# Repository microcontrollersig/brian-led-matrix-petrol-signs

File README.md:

# Big LED Matrix from Petrol Pump Signage

#### Info

Not the usual HUB08/HUB12/HUB40/HUB75 style setup. Inner workings [here](https://github.com/microcontrollersig/brian-led-matrix-petrol-signs/blob/main/REVERSEENGINEER.md)

They usually come in 6 panels wide, 2 panels height (effectively becomes a 96x32 single-color LED matrix)

# PCB Controller for LED matrix

#### Bill of Materials

| Qty |                                                                                                                                                                                             | Code                                                                                                          | Where to Buy                                                                                                                                                                                                                                                                                                                                                                                            | Required |
| --- | ------------------------------------------------------------------------------------------------------------------------------------------------------------------------------------------- | ------------------------------------------------------------------------------------------------------------- | ------------------------------------------------------------------------------------------------------------------------------------------------------------------------------------------------------------------------------------------------------------------------------------------------------------------------------------------------------------------------------------------------------- | -------- |
| 1   |                                                                                    | [Raspberry Pico](https://www.raspberrypi.org/documentation/rp2040/getting-started/)                           | [Pi Australia](https://raspberry.piaustralia.com.au/products/raspberry-pi-pico?variant=32587824070705)<br/>[Altronics](https://www.altronics.com.au/p/z6421-raspberry-pi-pico-microcontroller-board/)<br/>[Element 14](https://au.element14.com/raspberry-pi/raspberry-pi-pico/raspberry-pi-32bit-arm-cortex/dp/3643332)<br/>[Core Electronics](https://core-electronics.com.au/raspberry-pi-pico.html) | Y        |
| 1   |                                                                          | [ESP8266 Wemos D1 mini](https://www.wemos.cc/en/latest/d1/d1_mini.html)                                       | [Aliexpress - color: d1 mini](https://www.aliexpress.com/item/32651747570.html)                                                                                                                                                                                                                                                                                                                         | Y        |
| 1   |                                       | [16 Pin IDC Locking Vertical Header](https://www.jaycar.com.au/16-pin-idc-locking-vertical-header/p/PP1138)   | 16-pin ribbon header                                                                                                                                                                                                                                                                                                                                                                                    | Y        |
| 1   |                                                                  | [3.5A buck converter - color: 5V](https://www.aliexpress.com/item/33036075561.html)                           | Buck converter                                                                                                                                                                                                                                                                                                                                                                                          | Y        |
| 1   |                                                                                                                      | [Terminal block](https://www.altronics.com.au/p/p2041a-dinkle-3-way-5.08mm-pcb-mount-terminal-block/)         | External power source                                                                                                                                                                                                                                                                                                                                                                                   | Y        |
| 1   |                      | [Disk Drive Power Connector Socket](https://www.jaycar.com.au/disk-drive-power-connector-socket/p/PS0742)     | Power connector from LEDs to terminal block                                                                                                                                                                                                                                                                                                                                                             | N        |
| 1   |                                                 | [Female header](https://www.jaycar.com.au/40-pin-female-header-strip/p/HM3230)                                | Female header for Pico                                                                                                                                                                                                                                                                                                                                                                                  | Y        |
| 1   |                                             | [Right-angle connector ](https://www.rockby.com.au/CatresultsSql_12.cfm?select=33&subcode=142&stock_no=27464) | Need for connecting buck converter                                                                                                                                                                                                                                                                                                                                                                      | Y        |
| 1   |  | [Round Female Pin Header connector - snapable](https://www.aliexpress.com/item/32848204130.html)              | Aliexpress                                                                                                                                                                                                                                                                                                                                                                                              | N        |
| 1   |                                                           | [2N2222A NPN transistor](https://www.jaycar.com.au/2n2222a-npn-transistor/p/ZT2298)                           | Pico software-controlled reset switch                                                                                                                                                                                                                                                                                                                                                                   | N        |

#### EAGLE Schematic for PCB Board

#### EAGLE Board file for PCB Board

### PCB Top Layer

#### PCB Bottom Layer

#### Raspberry Pi Pico

#### ESP8266 wemos d1 mini

# Software

Steps needed to complete software setup:

- Firmware needs to be uploaded to Pico, firmware also need to be uploaded to esp8266 D1 mini.
- wifi configuration of D1 mini.

In order to complete these steps, must first do the following steps on your computer:

- Download zip file containing firmware files and CH340 Windows driver for D1 mini from [here](https://github.com/microcontrollersig/brian-led-matrix-petrol-signs/releases/latest/download/brian-petrol-signs-easy-firmware-upload.zip) . Unzip the file to a known location on your computer.
- Download a ESP8266 flash utility. There are a number available, my preferred one is ESPHome-Flasher, which can be
  downloaded from [here](https://github.com/esphome/esphome-flasher/releases) .

## Uploading firmware to Raspberry Pico

[Click here for details](https://github.com/microcontrollersig/brian-led-matrix-petrol-signs/tree/main/code/pico).

## Uploading firmware to D1 mini and configuring wifi

[Click here for details](https://github.com/microcontrollersig/brian-led-matrix-petrol-signs/tree/main/code/d1mini)

# Roles of Microprocessors

## Pico

- update LED matrix
- receive commands from the D1 mini via serial(RX).

## ESP8266 D1mini

- Present user with web interface for controlling LED matrix.
- Send commands for the Pico to execute on the LED matrix via Serial(TX).

# References

- [How LED matrix was reverse engineered](https://github.com/microcontrollersig/brian-led-matrix-petrol-signs/blob/main/REVERSEENGINEER.md)

- [Eagle files](https://github.com/microcontrollersig/brian-led-matrix-petrol-signs/tree/main/eagle)

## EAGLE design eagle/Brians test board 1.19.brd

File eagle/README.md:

# Eagle Files

Latest version is v1.18

# JLCPCB
[JLCPCB gerber viewer at checkout](https://cart.jlcpcb.com/quote?orderType=1&stencilWidth=100&stencilLength=100&stencilCounts=5&stencilLayer=2&stencilPly=1.6&steelmeshSellingPriceRecordNum=A8256537-5522-491C-965C-646F5842AEC9&purchaseNumber=)

[gerber viewer](https://www.pcbway.com/project/OnlineGerberViewer.html)

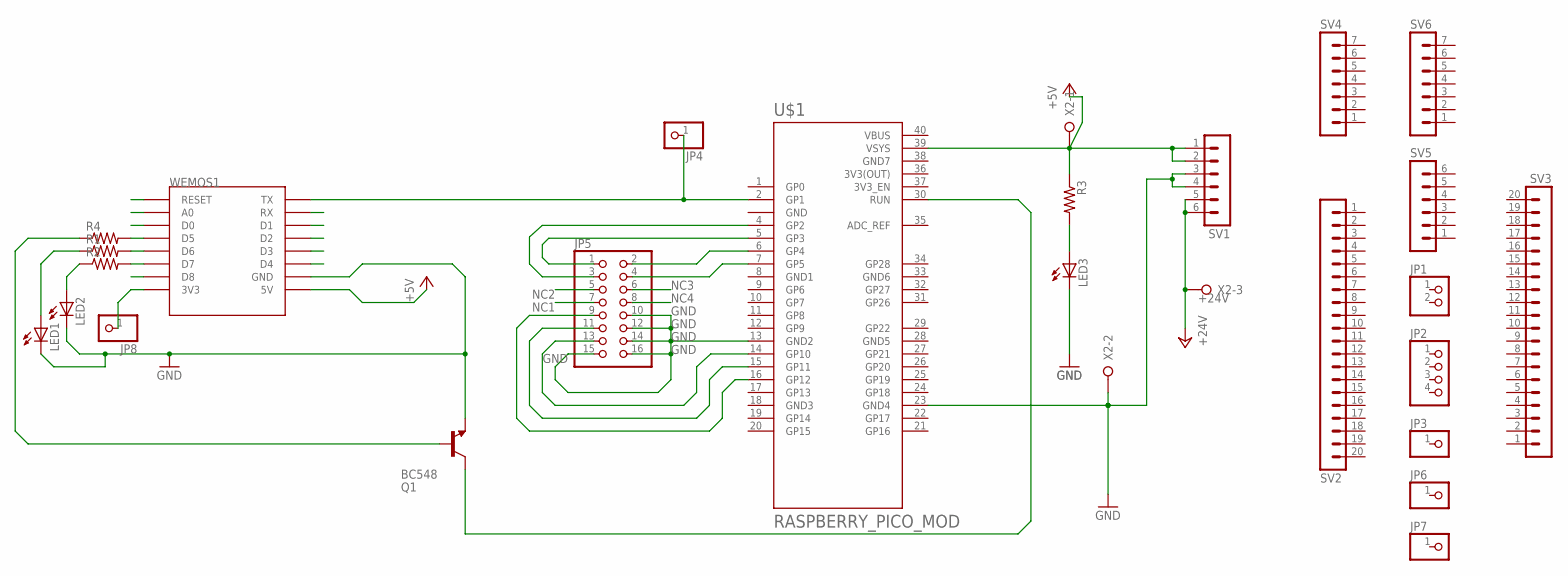
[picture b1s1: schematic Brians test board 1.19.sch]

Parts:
JP1: PINHD-1X2; 1X02
JP2: PINHD-1X4; 1X04
JP3, JP4, JP6, JP7, JP8: PINHD-1X1; 1X01
JP5: PINHD-2X8; 2X08
LED1, LED2, LED3: LED3MM
Q1: BC548; TO92-EBC
R1, R2, R4: R-US_0204/2V; 0204V
R3: R-US_0207/10; 0207/10
SV1, SV5: MA06-1
SV2, SV3: MA20-1
SV4, SV6: MA07-1
U$1: RASPBERRY_PICO_MOD; PICO-PKG-TH-LED
WEMOS1: WEMOS-D1-MINI
X2: W237-3E

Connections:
3V3(OUT): U$1.36 (3V3(OUT))
+5V: R3.1, SV1.1, SV1.2, U$1.39 (VSYS), WEMOS1.5V, X2.1
+24V: SV1.5, SV1.6, X2.3
A0: WEMOS1.A0
D0: WEMOS1.D0
D1: WEMOS1.D1
D2: WEMOS1.D2
D3: WEMOS1.D3
D4: WEMOS1.D4
D8: WEMOS1.D8
GND: JP5.10, JP5.12, JP5.14, JP5.15, JP5.16, LED1.K (C), LED2.K (C), LED3.K (C), Q1.E, SV1.3, SV1.4, U$1.3 (GND), U$1.13 (GND2), U$1.23 (GND4), WEMOS1.GND, X2.2
GND1: U$1.8 (GND1)
GND3: U$1.18 (GND3)
GND5: U$1.28 (GND5)
GND6: U$1.33 (GND6)
GND7: U$1.38 (GND7)
unnamed: JP5.1, U$1.5 (GP3)
unnamed: JP8.1, WEMOS1.3V3
unnamed: Q1.C, U$1.30 (RUN)
unnamed: JP4.1, U$1.2 (GP1), WEMOS1.TX
unnamed: JP5.3, U$1.4 (GP2)
unnamed: R2.2, WEMOS1.D7
unnamed: JP5.13, U$1.14 (GP10)
unnamed: JP5.11, U$1.15 (GP11)
unnamed: JP5.9, U$1.16 (GP12)
unnamed: JP5.2, U$1.6 (GP4)
unnamed: JP5.4, U$1.7 (GP5)
unnamed: R1.2, WEMOS1.D6
unnamed: LED2.A, R2.1
unnamed: LED1.A, R1.1
unnamed: LED3.A, R3.2
unnamed: R4.2, WEMOS1.D5
unnamed: Q1.B, R4.1
NC1: JP5.7
NC2: JP5.5
NC3: JP5.6
NC4: JP5.8
RST: WEMOS1.RESET
RX: WEMOS1.RX
VBUS: U$1.40 (VBUS)

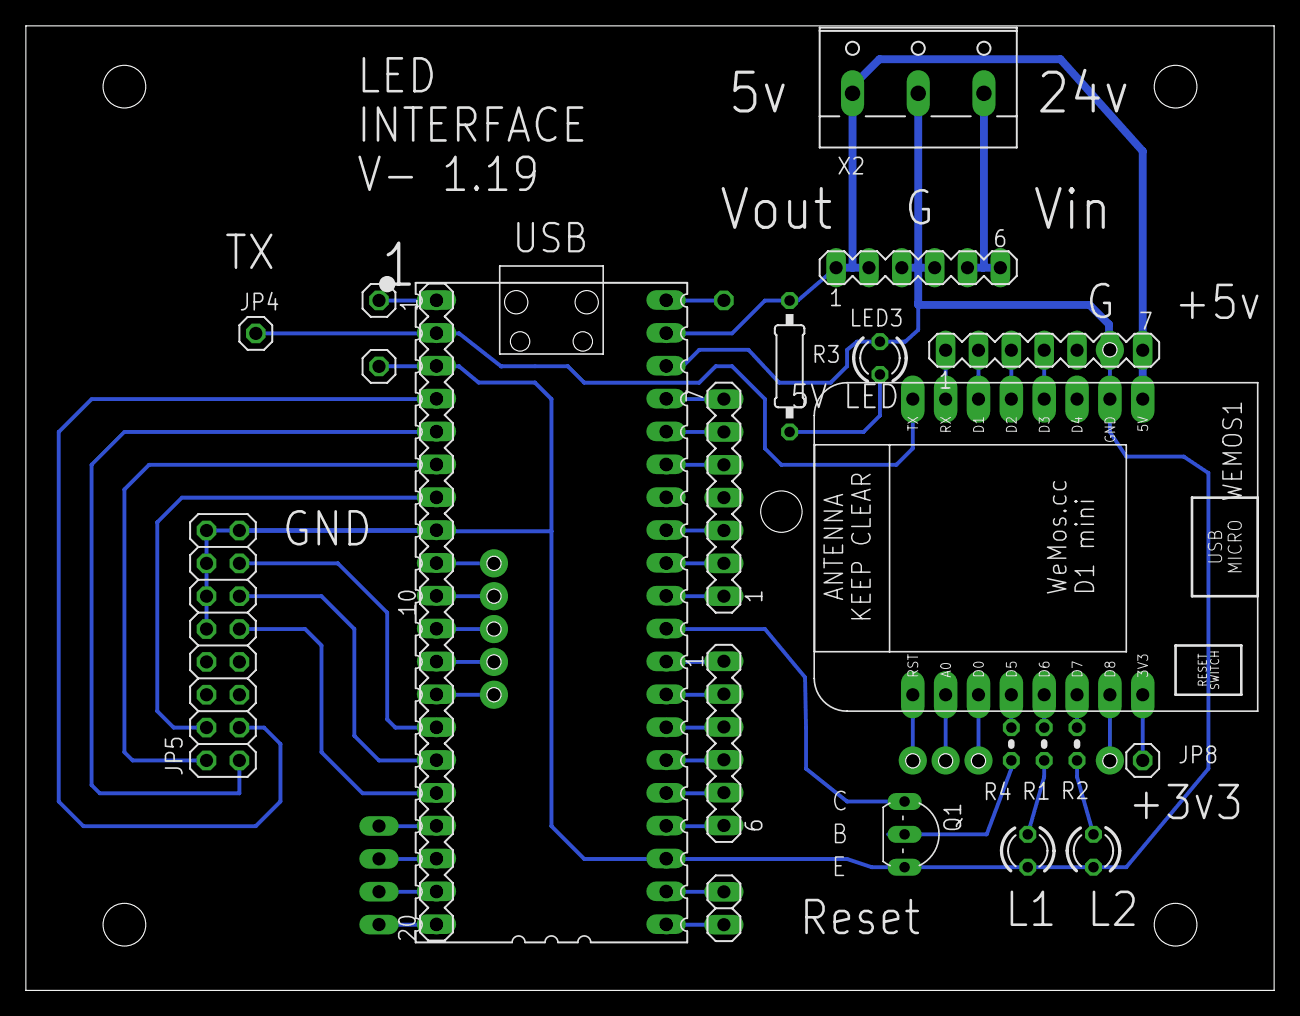
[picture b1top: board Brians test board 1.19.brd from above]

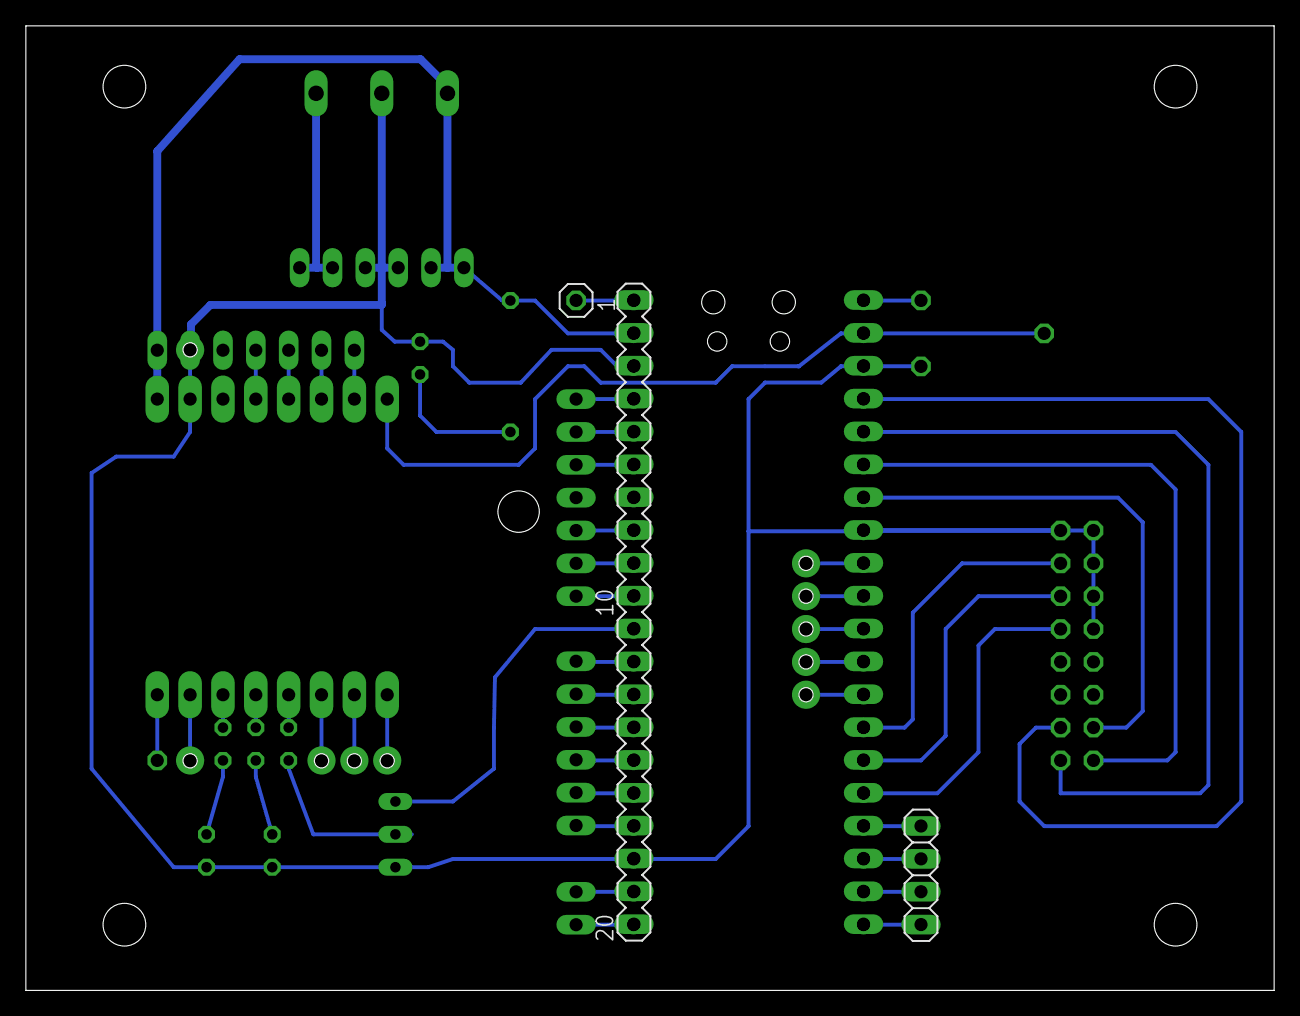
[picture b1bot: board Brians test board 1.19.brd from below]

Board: 2 copper layers, 96.5 x 74.6 mm, 25 parts (3 on the bottom side), 20 nets.

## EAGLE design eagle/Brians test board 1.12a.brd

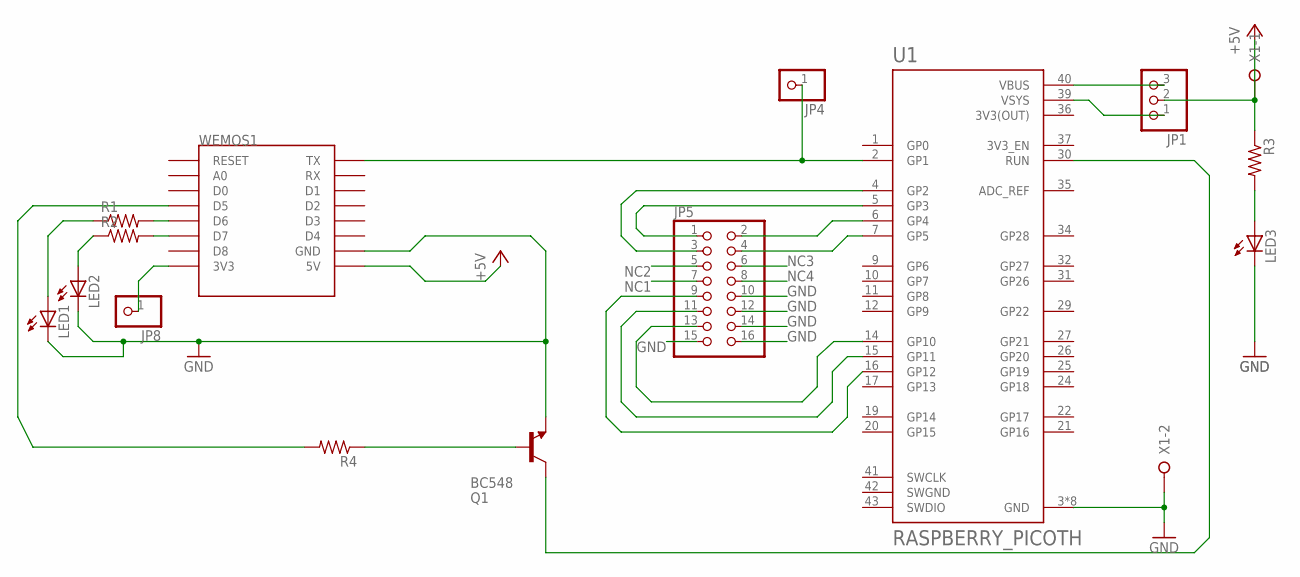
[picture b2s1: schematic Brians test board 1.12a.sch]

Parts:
JP1: PINHD-1X3; 1X03
JP4, JP8: PINHD-1X1; 1X01
JP5: PINHD-2X8; 2X08
LED1, LED2, LED3: LED3MM
Q1: BC548; TO92-EBC
R1, R2, R4: R-US_0204/2V; 0204V
R3: R-US_0207/10; 0207/10
U1: RASPBERRY_PICOTH; PICO-PKG-TH
WEMOS1: WEMOS-D1-MINI
X1: W237-02P; W237-132

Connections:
3V3(OUT): U1.36 (3V3(OUT))
+5V: JP1.2, R3.1, WEMOS1.5V, X1.1
GND: JP5.10, JP5.12, JP5.14, JP5.15, JP5.16, LED1.K (C), LED2.K (C), LED3.K (C), Q1.E, U1.3 (GND), U1.8 (GND), U1.13 (GND), U1.18 (GND), U1.23 (GND), U1.28 (GND), U1.33 (GND), U1.38 (GND), WEMOS1.GND, X1.2
unnamed: JP5.1, U1.5 (GP3)
unnamed: JP8.1, WEMOS1.3V3
unnamed: JP1.3, U1.40 (VBUS)
unnamed: Q1.C, U1.30 (RUN)
unnamed: JP4.1, U1.2 (GP1), WEMOS1.TX
unnamed: JP5.3, U1.4 (GP2)
unnamed: R2.2, WEMOS1.D7
unnamed: JP5.13, U1.14 (GP10)
unnamed: JP5.11, U1.15 (GP11)
unnamed: JP5.9, U1.16 (GP12)
unnamed: JP5.2, U1.6 (GP4)
unnamed: JP5.4, U1.7 (GP5)
unnamed: R1.2, WEMOS1.D6
unnamed: JP1.1, U1.39 (VSYS)
unnamed: LED2.A, R2.1
unnamed: LED1.A, R1.1
unnamed: LED3.A, R3.2
unnamed: R4.2, WEMOS1.D5
unnamed: Q1.B, R4.1
NC1: JP5.7
NC2: JP5.5
NC3: JP5.6
NC4: JP5.8
SWGND: U1.42 (SWGND)

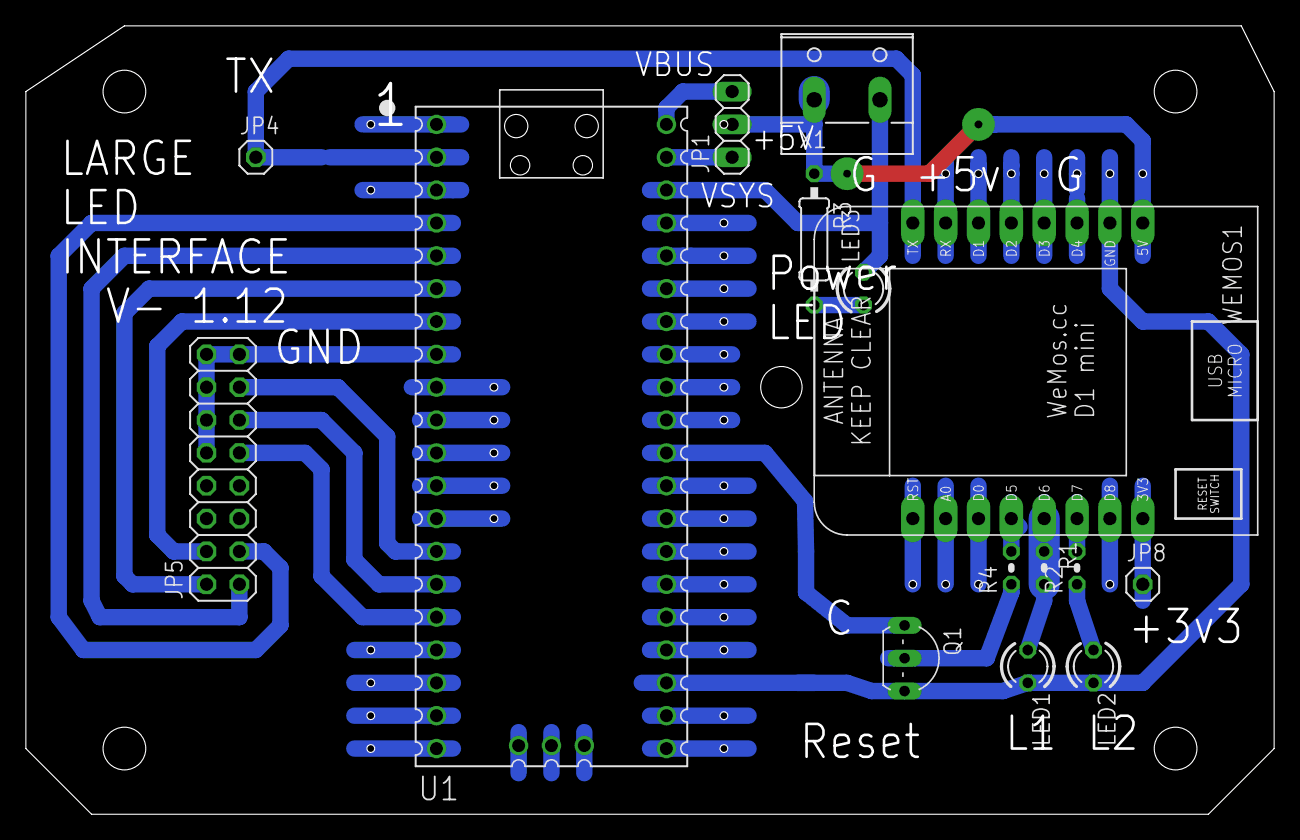
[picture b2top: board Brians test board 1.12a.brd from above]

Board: 2 copper layers, 96.5 x 61.0 mm, 15 parts (0 on the bottom side), 21 nets.

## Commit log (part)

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2021-06-13 cleanup code directory
2021-06-13 added new code directory
2021-06-13 add mutipanel demo
2021-06-20 single matrix now operational
2021-06-20 whole multiled panel (96x12) now operational
2021-06-30 Create script.LED Update
2021-06-30 Create script.LED Panel
2021-06-30 Rename script.LED Panel to script.LED Panel.yaml
2021-06-30 Rename script.LED Update to script.LED Update.yaml
2021-11-28 added rest books
2021-11-29 fixed npm config
2021-11-29 rebuild games bundle
2021-11-29 dino changes
2021-11-30 checking behaviour of text and scrolling text
2021-11-30 add spacing between chars in small font
2021-11-30 simple scroll command now accepts small font
2021-11-30 scrolling text small font
2021-12-01 add menu for apps and games
2021-12-01 up arrow sort of works in dino
2021-12-02 tetris time handling am correctly now
2021-12-05 move IP address display to top line
2021-12-05 panel size can be modified in captive portal
2021-12-05 brian's christmas tree
2021-12-05 screenshots
2021-12-06 add readme for screenshots
2021-12-06 ability to modify panel size in captive portal
2021-12-06 added subcommand for changing panel size
2021-12-07 Major bug if panel size width > 6 investigating
2021-12-07 panel size > 6 bug fixed
2021-12-07 panel size accomodation
2021-12-07 forgot to delete after create dynamic char array
2021-12-07 changed timeout
2021-12-08 add reset command to pico
2021-12-08 panel size sent to pico
2021-12-08 saving new panel size in d1 mini
2021-12-11 pico panel size stroage now stable
2021-12-11 changed screenshot of PCB on front page
2021-12-11 fixup
2021-12-11 add riplple effect to button
2021-12-12 validate panel size
2021-12-12 pico: added one line scroll
2021-12-13 scrolling text fixes
2021-12-14 one line scrolling text introduced
2021-12-14 vertical positioning of scrolling text
2021-12-15 defaults for y position of one line scrolling text
2021-12-15 one line scrolling implemented
2021-12-17 panel size reflected in captive portal
